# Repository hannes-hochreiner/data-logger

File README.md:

# data-logger
Gadget writing sensor data to an SD card.

## TODOs
  * update design rules and re-run DRC

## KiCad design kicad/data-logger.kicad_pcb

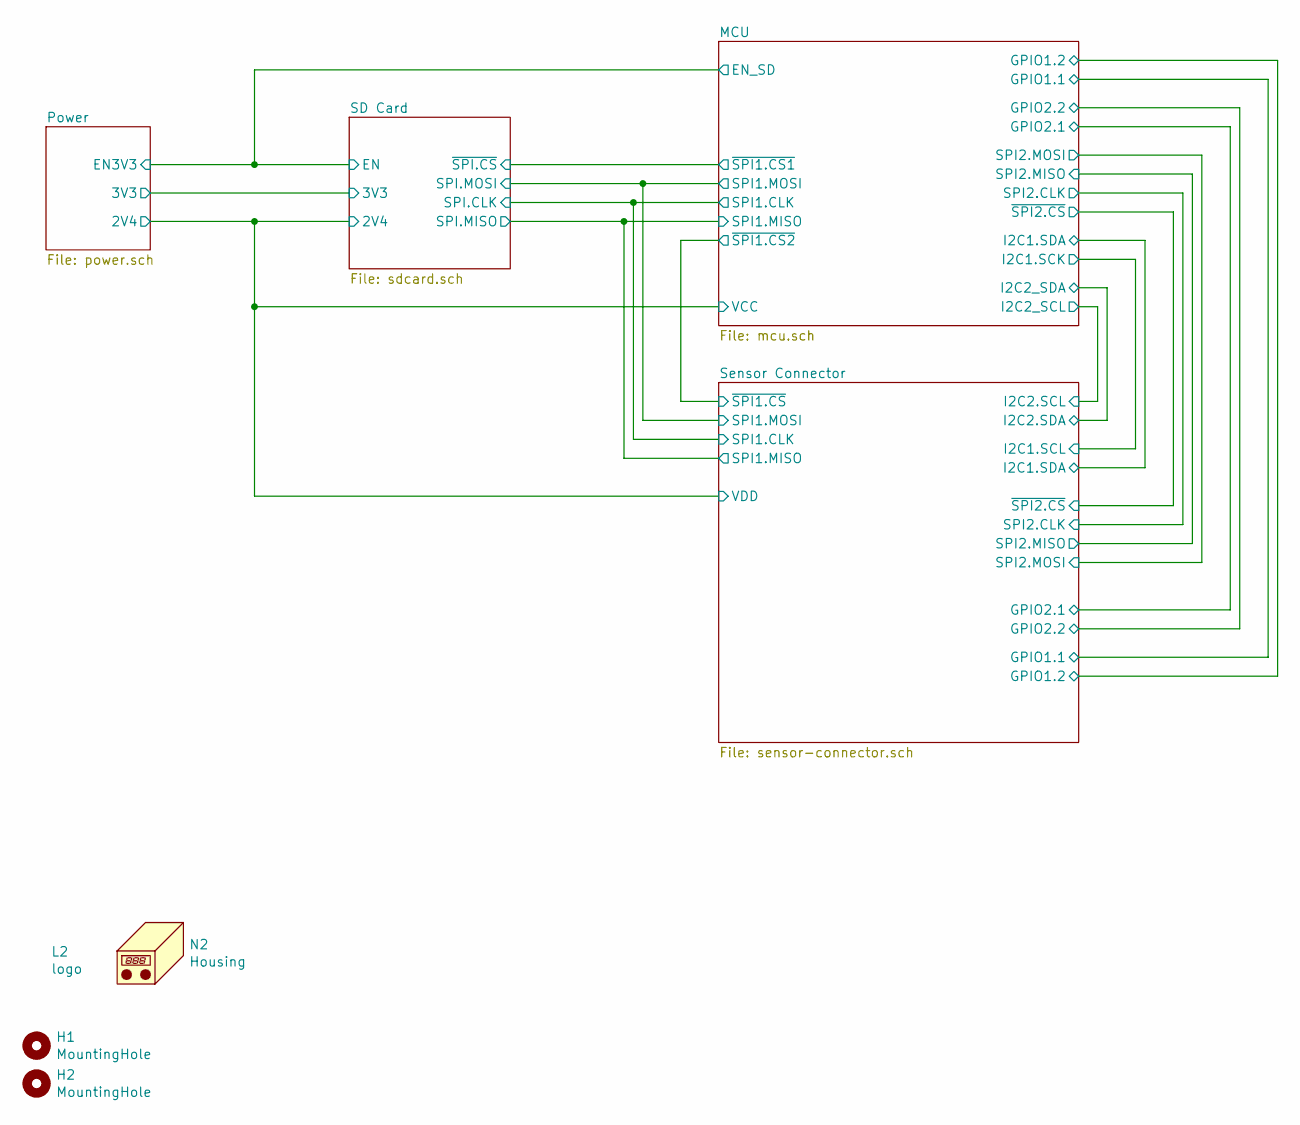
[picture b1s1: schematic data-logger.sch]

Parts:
H1, H2: MountingHole; MountingHole_2.7mm_M2.5_Pad_Via
L2: logo
N2: Housing; pcb_outline

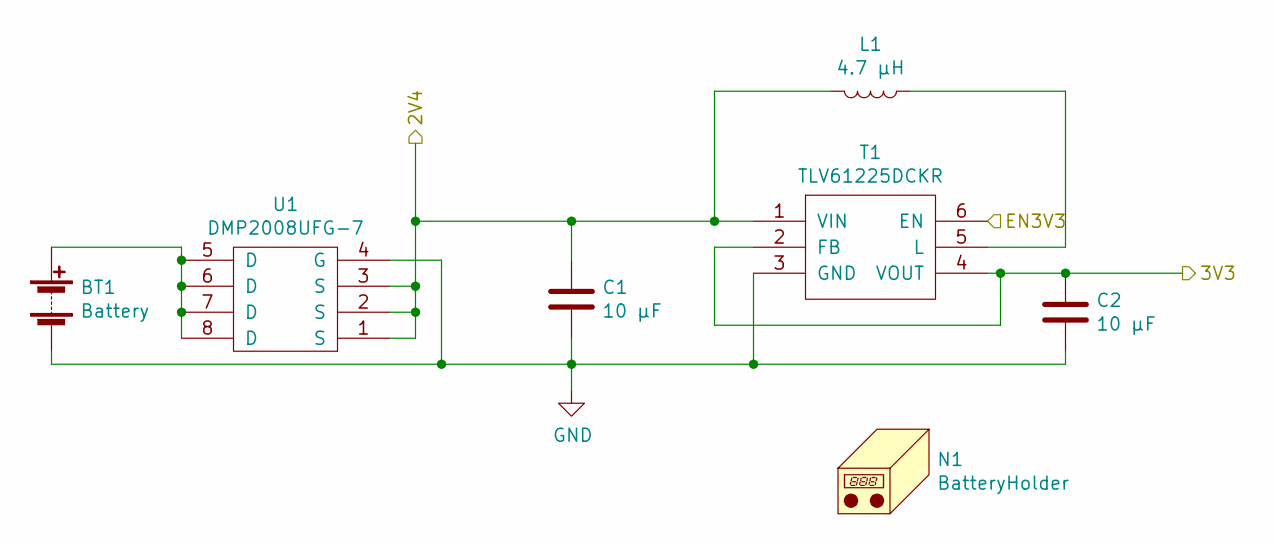
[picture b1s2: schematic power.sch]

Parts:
BT1: Battery; PinSocket_1x02_P2.54mm_Horizontal; DigiKey_PartNumber SAM1225-02-ND
C1, C2: 10 µF; C_0603_1608Metric
L1: 4.7 µH; LQH3NPN4R7MMEL; DigiKey_PartNumber 490-15954-1-ND
N1: BatteryHolder; MPD_BC2AAAL; DigiKey_PartNumber BC2AAAL-ND
T1: TLV61225DCKR; DigiKey_PartNumber 296-36756-1-ND
U1: DMP2008UFG-7; DigiKey_PartNumber DMP2008UFG-7DICT-ND

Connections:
/Power/2V4: C1.1, L1.2, T1.1 (VIN), U1.1 (S), U1.2 (S), U1.3 (S); also elsewhere on the board
/Power/3V3: C2.1, T1.2 (FB), T1.4 (VOUT); also elsewhere on the board
/SD Card/EN: T1.6 (EN); also elsewhere on the board
GND: BT1.2 (-), C1.2, C2.2, T1.3 (GND), U1.4 (G); also elsewhere on the board
unnamed: BT1.1 (+), U1.5 (D), U1.6 (D), U1.7 (D), U1.8 (D)
unnamed: L1.1, T1.5 (L)

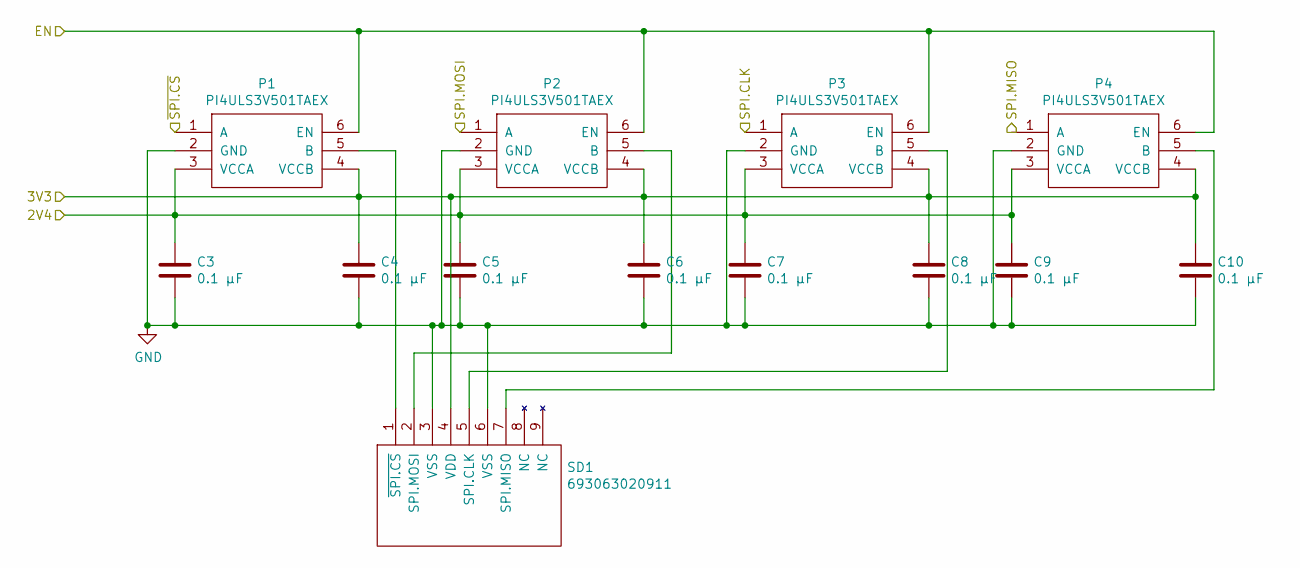
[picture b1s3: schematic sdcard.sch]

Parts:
C3, C4, C5, C6, C7, C8, C9, C10: 0.1 µF; C_0603_1608Metric
P1, P2, P3, P4: PI4ULS3V501TAEX; SOT-23-6; DigiKey_PartNumber PI4ULS3V501TAEXDICT-ND
SD1: 693063020911; DigiKey_PartNumber 732-3818-1-ND

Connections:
/Power/2V4: C3.1, C5.1, C7.1, C9.1, P1.3 (VCCA), P2.3 (VCCA), P3.3 (VCCA), P4.3 (VCCA); also elsewhere on the board
/Power/3V3: C4.1, C6.1, C8.1, C10.1, P1.4 (VCCB), P2.4 (VCCB), P3.4 (VCCB), P4.4 (VCCB), SD1.4 (VDD); also elsewhere on the board
/SD Card/EN: P1.6 (EN), P2.6 (EN), P3.6 (EN), P4.6 (EN); also elsewhere on the board
/SD Card/SPI.CLK: P3.1 (A); also elsewhere on the board
/SD Card/SPI.MISO: P4.1 (A); also elsewhere on the board
/SD Card/SPI.MOSI: P2.1 (A); also elsewhere on the board
/SD Card/~SPI.CS: P1.1 (A); also elsewhere on the board
GND: C3.2, C4.2, C5.2, C6.2, C7.2, C8.2, C9.2, C10.2, P1.2 (GND), P2.2 (GND), P3.2 (GND), P4.2 (GND), SD1.3 (VSS), SD1.6 (VSS); also elsewhere on the board
unnamed: P1.5 (B), SD1.1 (~SPI.CS)
unnamed: P2.5 (B), SD1.2 (SPI.MOSI)
unnamed: P3.5 (B), SD1.5 (SPI.CLK)
unnamed: P4.5 (B), SD1.7 (SPI.MISO)

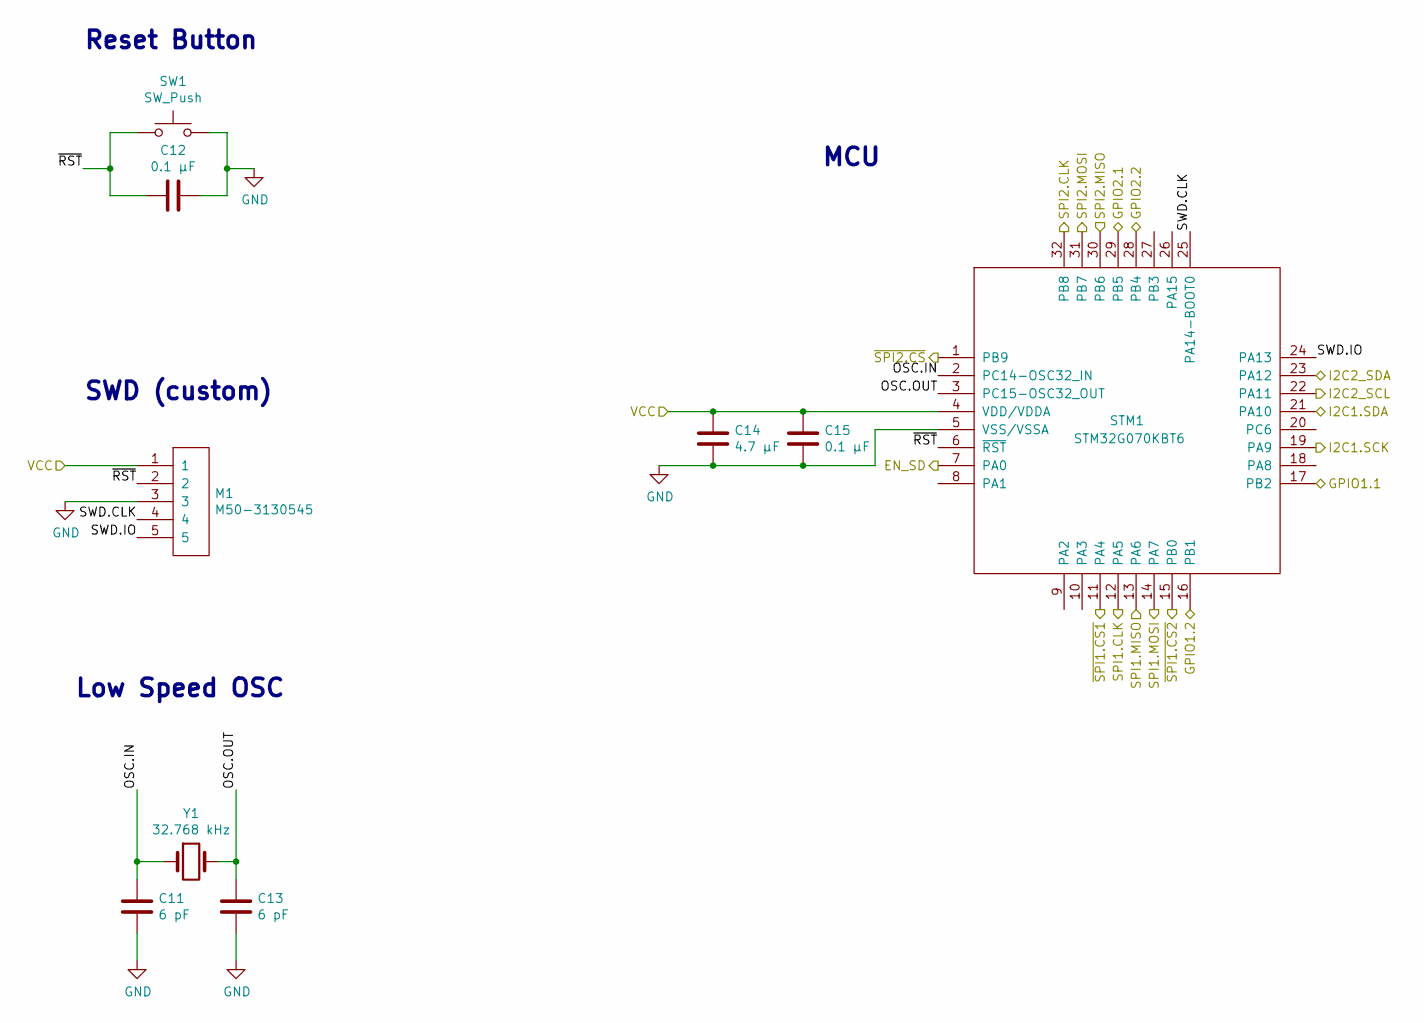
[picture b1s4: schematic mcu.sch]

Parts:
C11, C13: 6 pF; C_0603_1608Metric; DigiKey_PartNumber 311-1055-1-ND
C12, C15: 0.1 µF; C_0603_1608Metric
C14: 4.7 µF; C_0603_1608Metric
M1: M50-3130545; Manufacturer_PartNumber M50-3130545; DigiKey_PartNumber 952-3585-ND
STM1: STM32G070KBT6; LQFP-32_7x7mm_P0.8mm; DigiKey_PartNumber 497-STM32G070KBT6-ND
SW1: SW_Push; PTS526-SM15-SMTR2-LFS; DigiKey_PartNumber CKN12220-1-ND
Y1: 32.768 kHz; CM7V-T1A; DigiKey_PartNumber 2195-CM7V-T1A-32.768KHZ-6PF-20PPM-TA-QC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

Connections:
/MCU/GPIO1.1: STM1.17 (PB2); also elsewhere on the board
/MCU/GPIO1.2: STM1.16 (PB1); also elsewhere on the board
/MCU/GPIO2.1: STM1.29 (PB5); also elsewhere on the board
/MCU/GPIO2.2: STM1.28 (PB4); also elsewhere on the board
/MCU/I2C1.SCK: STM1.19 (PA9); also elsewhere on the board
/MCU/I2C1.SDA: STM1.21 (PA10); also elsewhere on the board
/MCU/OSC.IN: C11.1, STM1.2 (PC14-OSC32_IN), Y1.1
/MCU/OSC.OUT: C13.1, STM1.3 (PC15-OSC32_OUT), Y1.2
/MCU/SPI2.CLK: STM1.32 (PB8); also elsewhere on the board
/MCU/SPI2.MISO: STM1.30 (PB6); also elsewhere on the board
/MCU/SPI2.MOSI: STM1.31 (PB7); also elsewhere on the board
/MCU/SWD.CLK: M1.4, STM1.25 (PA14-BOOT0)
/MCU/SWD.IO: M1.5, STM1.24 (PA13)
/MCU/~RST: C12.2, M1.2, STM1.6 (~RST), SW1.1
/MCU/~SPI2.CS: STM1.1 (PB9); also elsewhere on the board
/Power/2V4: C14.1, C15.1, M1.1, STM1.4 (VDD/VDDA); also elsewhere on the board
/SD Card/EN: STM1.7 (PA0); also elsewhere on the board
/SD Card/SPI.CLK: STM1.12 (PA5); also elsewhere on the board
/SD Card/SPI.MISO: STM1.13 (PA6); also elsewhere on the board
/SD Card/SPI.MOSI: STM1.14 (PA7); also elsewhere on the board
/SD Card/~SPI.CS: STM1.11 (PA4); also elsewhere on the board
/Sensor Connector/I2C2.SCL: STM1.22 (PA11); also elsewhere on the board
/Sensor Connector/I2C2.SDA: STM1.23 (PA12); also elsewhere on the board
/Sensor Connector/~SPI1.CS: STM1.15 (PB0); also elsewhere on the board
GND: C11.2, C12.1, C13.2, C14.2, C15.2, M1.3, STM1.5 (VSS/VSSA), SW1.2; also elsewhere on the board

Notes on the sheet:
SWD (custom)
Reset Button
Low Speed OSC
MCU

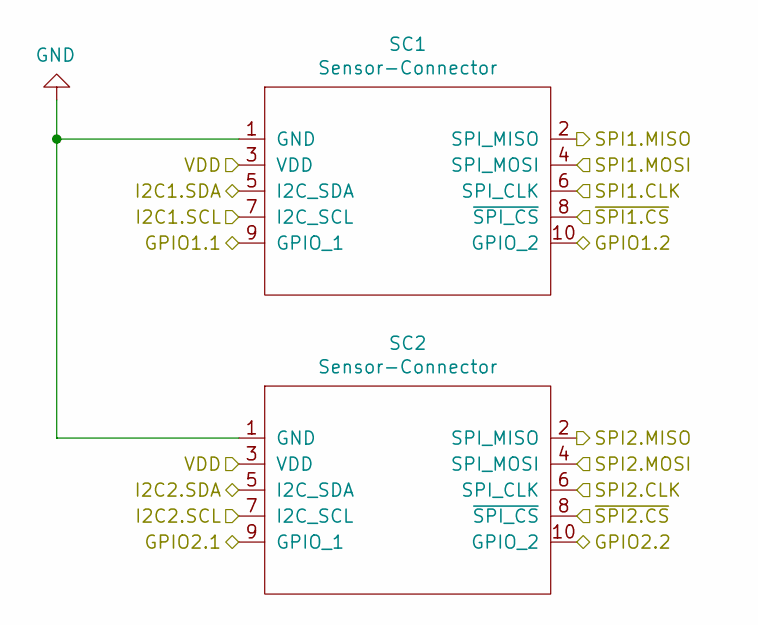
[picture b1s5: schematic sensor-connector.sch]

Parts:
SC1, SC2: Sensor-Connector; M50-3150542R

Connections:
/MCU/GPIO1.1: SC1.9 (GPIO_1); also elsewhere on the board
/MCU/GPIO1.2: SC1.10 (GPIO_2); also elsewhere on the board
/MCU/GPIO2.1: SC2.9 (GPIO_1); also elsewhere on the board
/MCU/GPIO2.2: SC2.10 (GPIO_2); also elsewhere on the board
/MCU/I2C1.SCK: SC1.7 (I2C_SCL); also elsewhere on the board
/MCU/I2C1.SDA: SC1.5 (I2C_SDA); also elsewhere on the board
/MCU/SPI2.CLK: SC2.6 (SPI_CLK); also elsewhere on the board
/MCU/SPI2.MISO: SC2.2 (SPI_MISO); also elsewhere on the board
/MCU/SPI2.MOSI: SC2.4 (SPI_MOSI); also elsewhere on the board
/MCU/~SPI2.CS: SC2.8 (~SPI_CS); also elsewhere on the board
/Power/2V4: SC1.3 (VDD), SC2.3 (VDD); also elsewhere on the board
/SD Card/SPI.CLK: SC1.6 (SPI_CLK); also elsewhere on the board
/SD Card/SPI.MISO: SC1.2 (SPI_MISO); also elsewhere on the board
/SD Card/SPI.MOSI: SC1.4 (SPI_MOSI); also elsewhere on the board
/Sensor Connector/I2C2.SCL: SC2.7 (I2C_SCL); also elsewhere on the board
/Sensor Connector/I2C2.SDA: SC2.5 (I2C_SDA); also elsewhere on the board
/Sensor Connector/~SPI1.CS: SC1.8 (~SPI_CS); also elsewhere on the board
GND: SC1.1 (GND), SC2.1 (GND); also elsewhere on the board

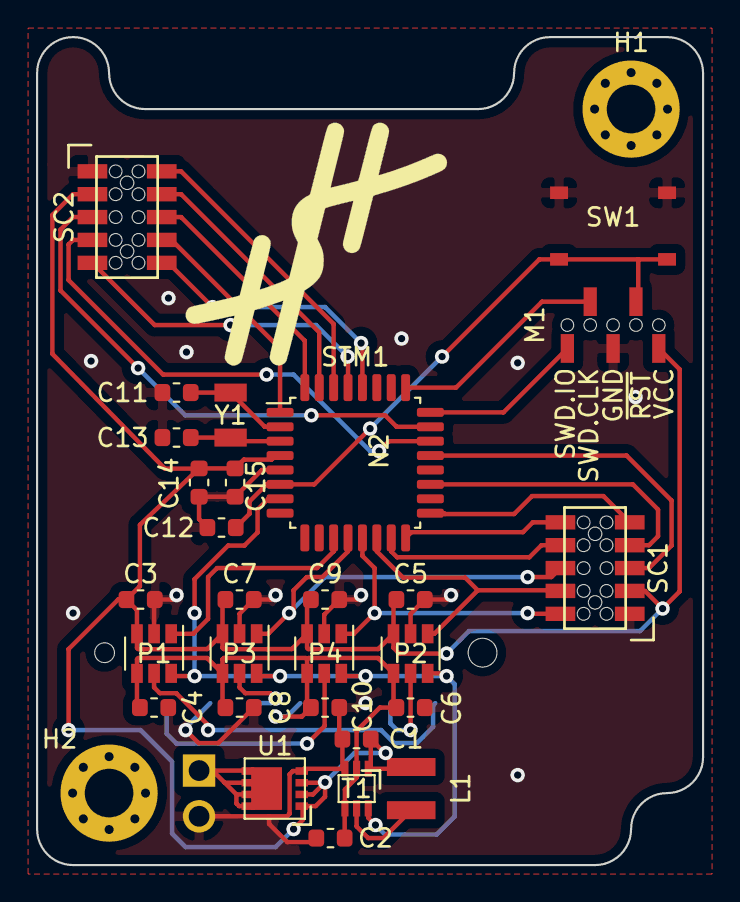
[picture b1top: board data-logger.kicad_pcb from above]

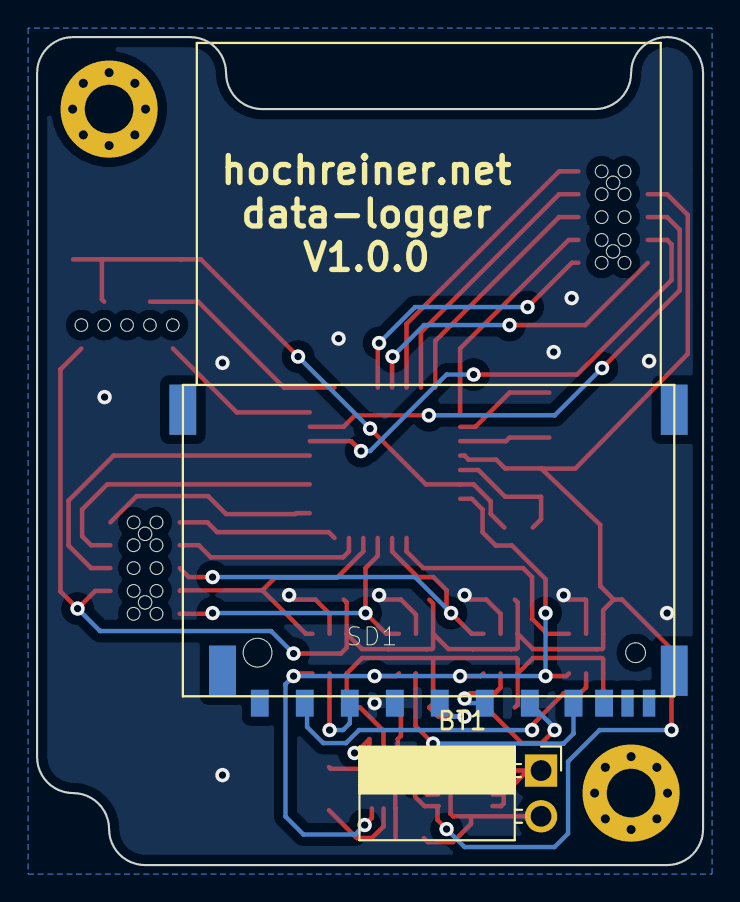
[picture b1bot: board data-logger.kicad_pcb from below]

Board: 2 copper layers, 37.0 x 46.0 mm, 35 parts (3 on the bottom side), 32 nets.

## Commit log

2020-05-24 initial design completed
2020-05-25 added reverse polarization protection
2020-05-25 tweaks after drc
2020-05-25 updated todos
2020-05-25 updated sensor connector footprint
2020-05-25 added label
2020-05-25 added labels
2020-05-25 switched the size of C14
2020-06-04 added info about first tests
2020-06-05 added images
2020-06-14 added successful SD card tests
2020-06-20 added improvemnts and new tests
2020-06-20 added tests
2020-06-20 moved half populated image to new section
2020-06-20 added an improvement idea
2020-06-21 updated tests
2020-06-23 updated sensor test status
